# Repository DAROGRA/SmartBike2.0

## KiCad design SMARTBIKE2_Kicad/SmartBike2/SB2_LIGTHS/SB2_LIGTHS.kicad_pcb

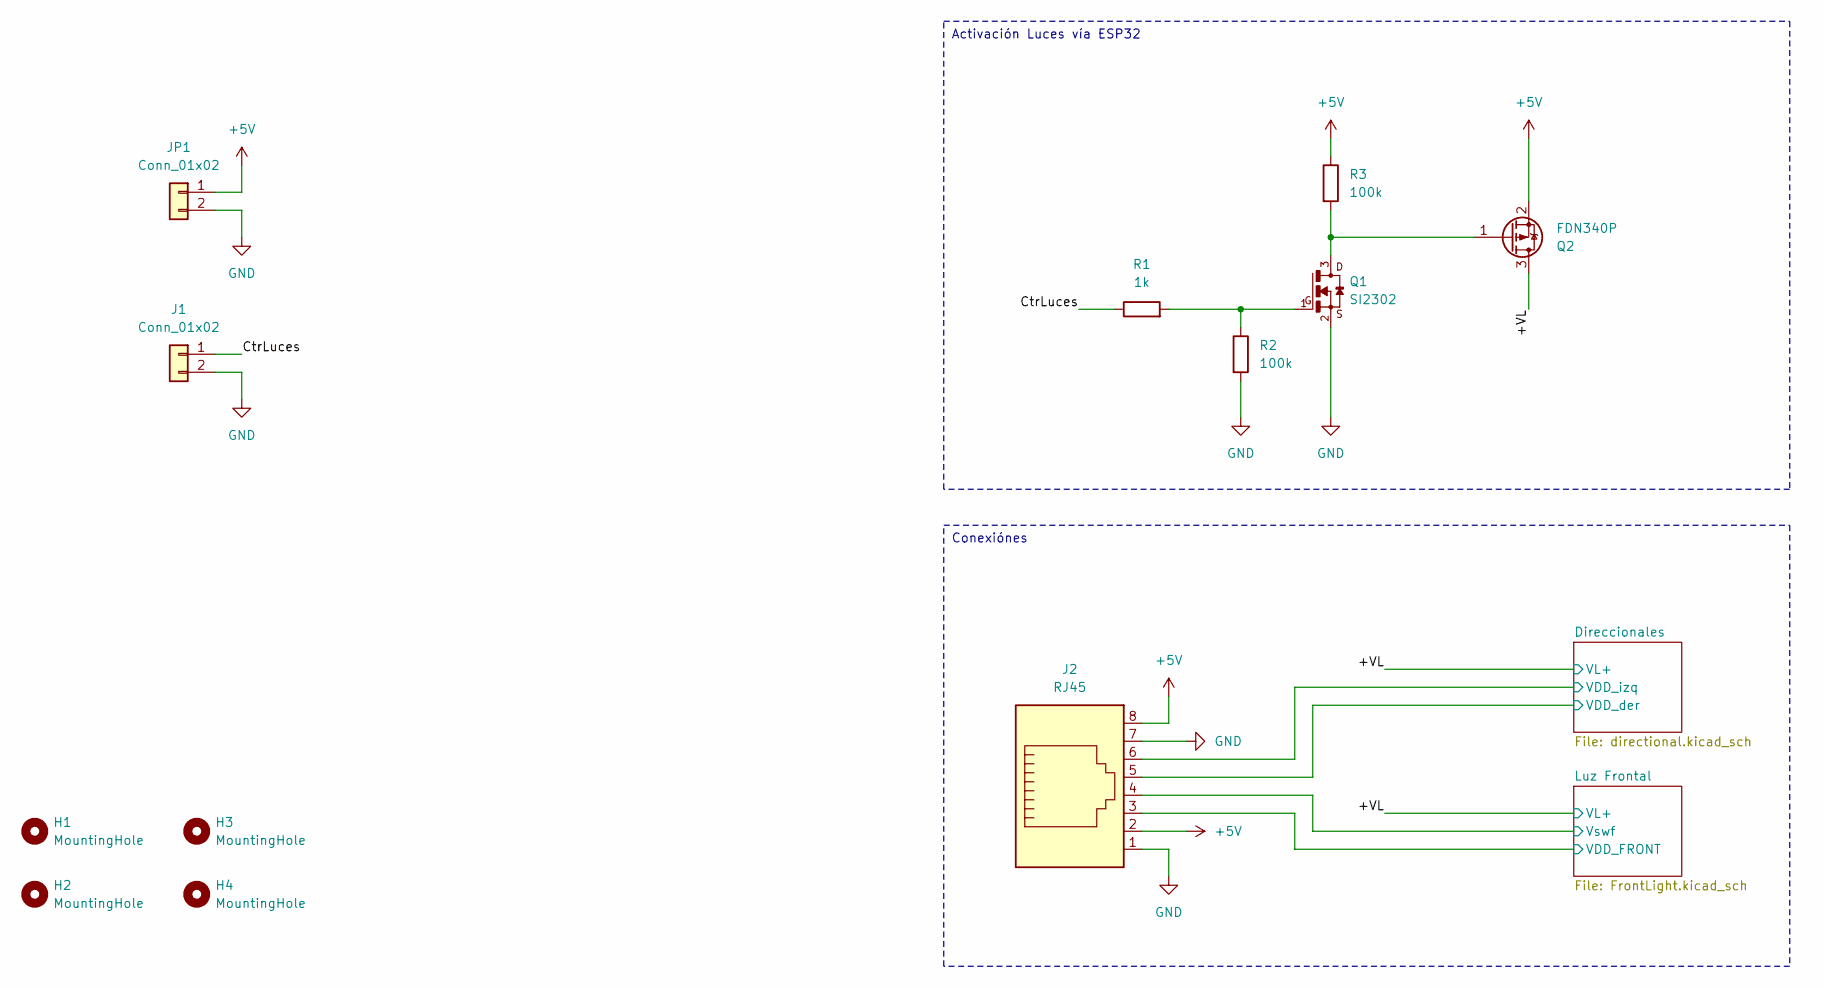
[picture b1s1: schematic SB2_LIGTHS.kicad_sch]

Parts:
H1, H2, H3, H4: MountingHole; MountingHole_2.2mm_M2
J1: Conn_01x02; JST_XH_B2B-XH-A_1x02_P2.50mm_Vertical
J2: RJ45; RJ45_Amphenol_RJHSE538X
JP1: Conn_01x02; JST_XH_B2B-XH-A_1x02_P2.50mm_Vertical
Q1: SI2302; SOT-23
Q2: FDN340P; SuperSOT-3
R1: 1k; R_0805_2012Metric_Pad1.20x1.40mm_HandSolder
R2, R3: 100k; R_0805_2012Metric_Pad1.20x1.40mm_HandSolder

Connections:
+5V: J2.2, J2.8, JP1.1, Q2.2 (S), R3.1
/+VL: Q2.3 (D); also elsewhere on the board
/CtrLuces: J1.1, R1.1
/Direccionales/VDD_der: J2.5; also elsewhere on the board
/Direccionales/VDD_izq: J2.6; also elsewhere on the board
/Luz Frontal/VDD_FRONT: J2.3; also elsewhere on the board
/Luz Frontal/Vswf: J2.4; also elsewhere on the board
GND: J1.2, J2.1, J2.7, JP1.2, Q1.2, R2.2; also elsewhere on the board
unnamed: Q1.1, R1.2, R2.1
unnamed: Q1.3, Q2.1 (G), R3.2

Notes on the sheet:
Activación Luces vía ESP32
Conexiónes

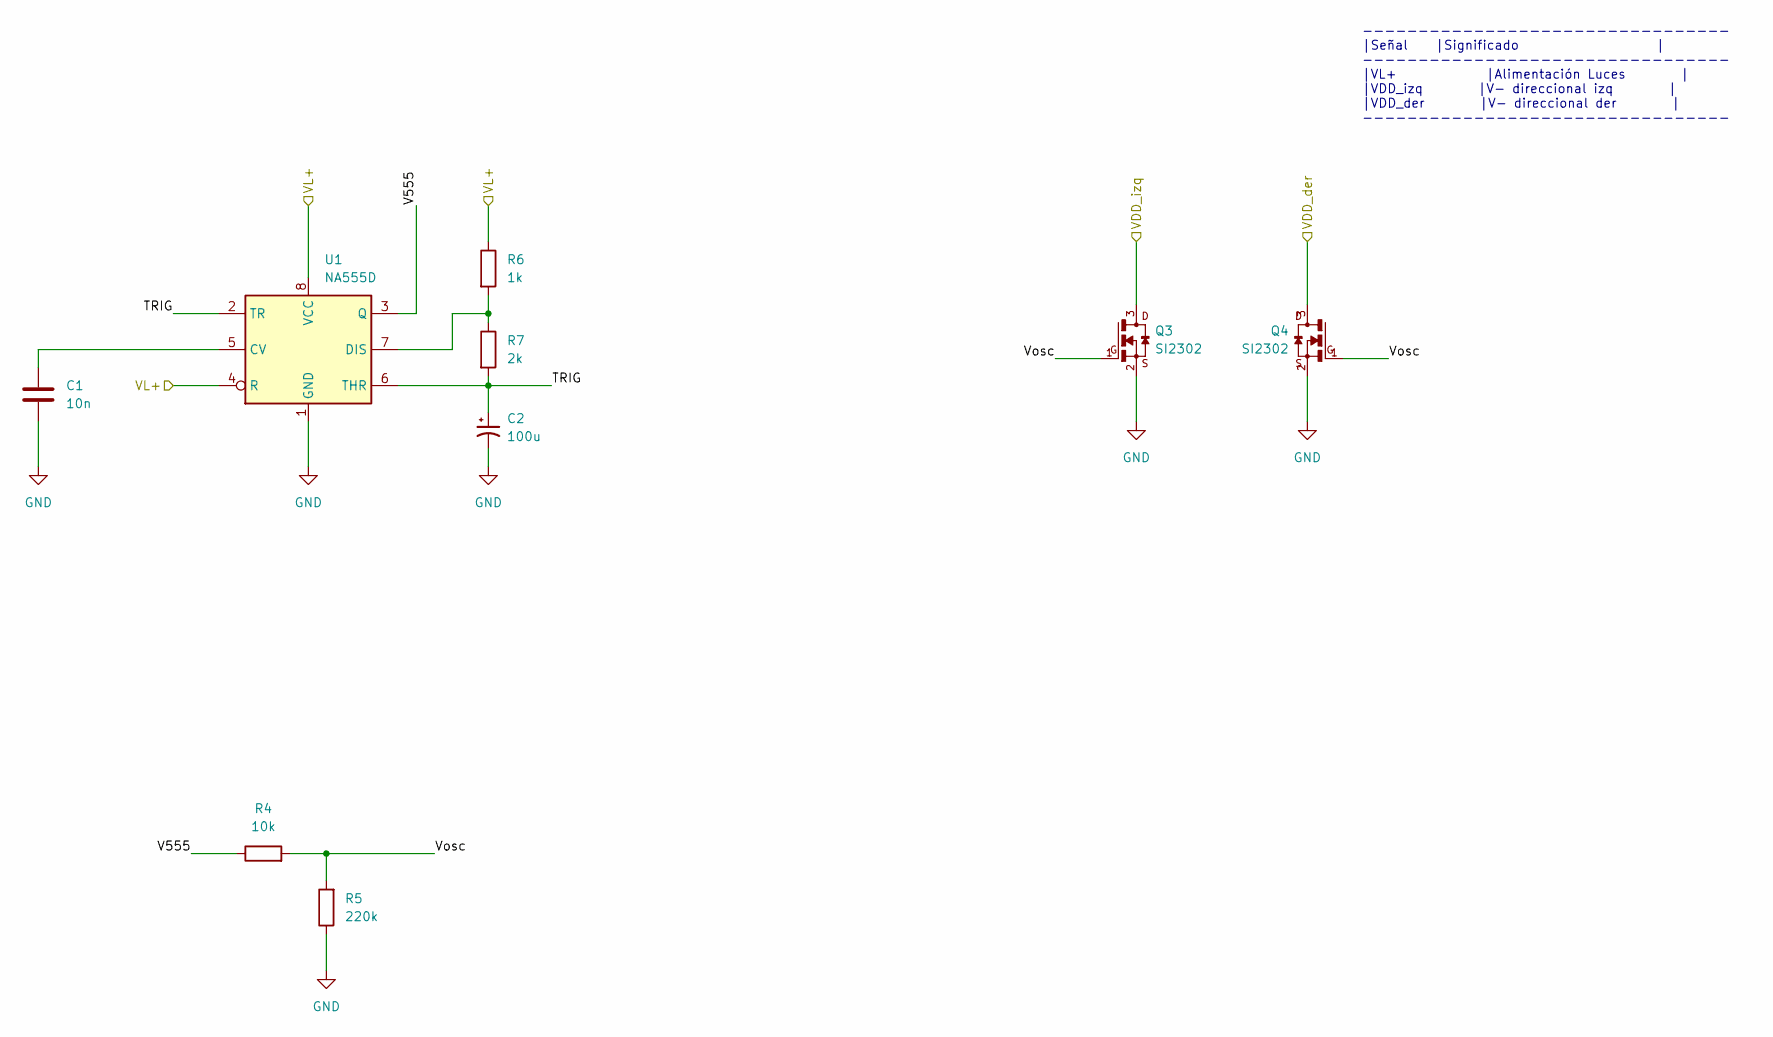
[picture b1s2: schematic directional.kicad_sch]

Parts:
C1: 10n; C_0805_2012Metric_Pad1.18x1.45mm_HandSolder
C2: 100u; CP_Elec_6.3x5.4
Q3, Q4: SI2302; SOT-23
R4: 10k; R_0805_2012Metric_Pad1.20x1.40mm_HandSolder
R5: 220k; R_0805_2012Metric_Pad1.20x1.40mm_HandSolder
R6: 1k; R_0805_2012Metric_Pad1.20x1.40mm_HandSolder
R7: 2k; R_0805_2012Metric_Pad1.20x1.40mm_HandSolder
U1: NA555D; SOIC-8_3.9x4.9mm_P1.27mm

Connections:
/+VL: R6.1, U1.4 (R), U1.8 (VCC); also elsewhere on the board
/Direccionales/TRIG: C2.1, R7.2, U1.2 (TR), U1.6 (THR)
/Direccionales/V555: R4.1, U1.3 (Q)
/Direccionales/VDD_der: Q4.3; also elsewhere on the board
/Direccionales/VDD_izq: Q3.3; also elsewhere on the board
/Direccionales/Vosc: Q3.1, Q4.1, R4.2, R5.2
GND: C1.2, C2.2, Q3.2, Q4.2, R5.1, U1.1 (GND); also elsewhere on the board
unnamed: C1.1, U1.5 (CV)
unnamed: R6.2, R7.1, U1.7 (DIS)

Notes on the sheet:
--------------------------------- |Señal |Significado | --------------------------------- |VL+ |Alimentación Luces | |VDD_izq |V- direccional izq | |VDD_der |V- direccional der | ---------------------------------

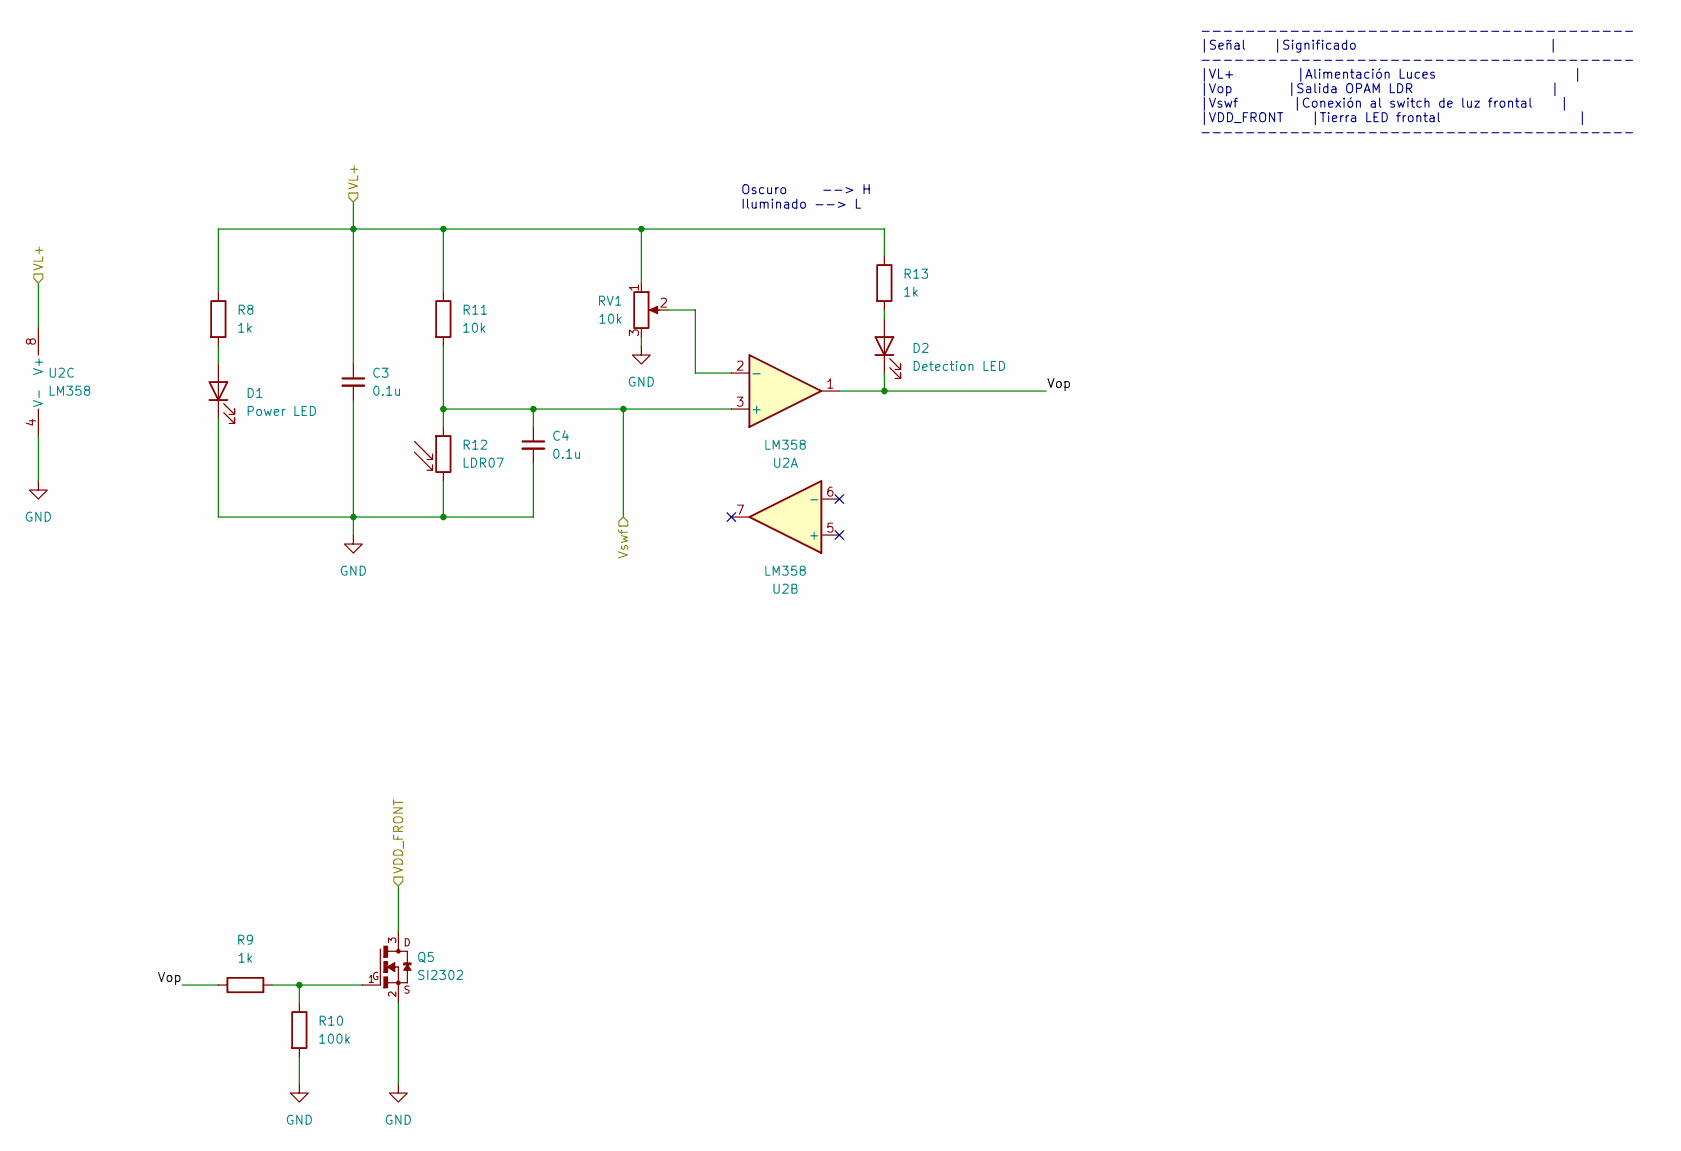
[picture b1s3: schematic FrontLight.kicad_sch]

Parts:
C3, C4: 0.1u; C_0805_2012Metric_Pad1.18x1.45mm_HandSolder
D1: Power LED; LED_1206_3216Metric_Pad1.42x1.75mm_HandSolder
D2: Detection LED; LED_1206_3216Metric_Pad1.42x1.75mm_HandSolder
Q5: SI2302; SOT-23
R8, R9, R13: 1k; R_0805_2012Metric_Pad1.20x1.40mm_HandSolder
R10: 100k; R_0805_2012Metric_Pad1.20x1.40mm_HandSolder
R11: 10k; R_0805_2012Metric_Pad1.20x1.40mm_HandSolder
R12: LDR07; R_LDR_5.1x4.3mm_P3.4mm_Vertical
RV1: 10k; Potentiometer_Bourns_3386P_Vertical
U2: LM358; SO-8_3.9x4.9mm_P1.27mm

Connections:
/+VL: C3.1, R8.1, R11.1, R13.1, RV1.1, U2.8 (V+); also elsewhere on the board
/Luz Frontal/VDD_FRONT: Q5.3; also elsewhere on the board
/Luz Frontal/Vop: D2.1 (K), R9.1, U2.1
/Luz Frontal/Vswf: C4.1, R11.2, R12.1, U2.3 (+); also elsewhere on the board
GND: C3.2, C4.2, D1.1 (K), Q5.2, R10.2, R12.2, RV1.3, U2.4 (V-); also elsewhere on the board
unnamed: D1.2 (A), R8.2
unnamed: D2.2 (A), R13.2
unnamed: Q5.1, R9.2, R10.1
unnamed: RV1.2, U2.2 (-)

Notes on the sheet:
Oscuro --> H Iluminado --> L
--------------------------------------- |Señal |Significado | --------------------------------------- |VL+ |Alimentación Luces | |Vop |Salida OPAM LDR | |Vswf |Conexión al switch de luz frontal | |VDD_FRONT |Tierra LED frontal | ---------------------------------------

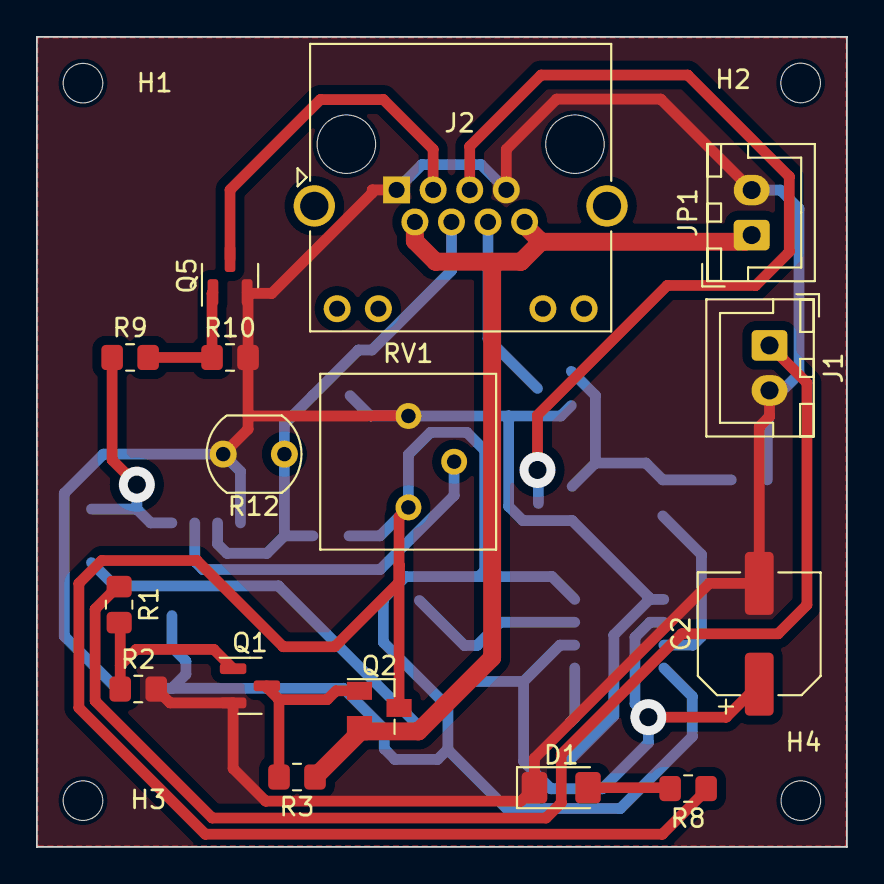
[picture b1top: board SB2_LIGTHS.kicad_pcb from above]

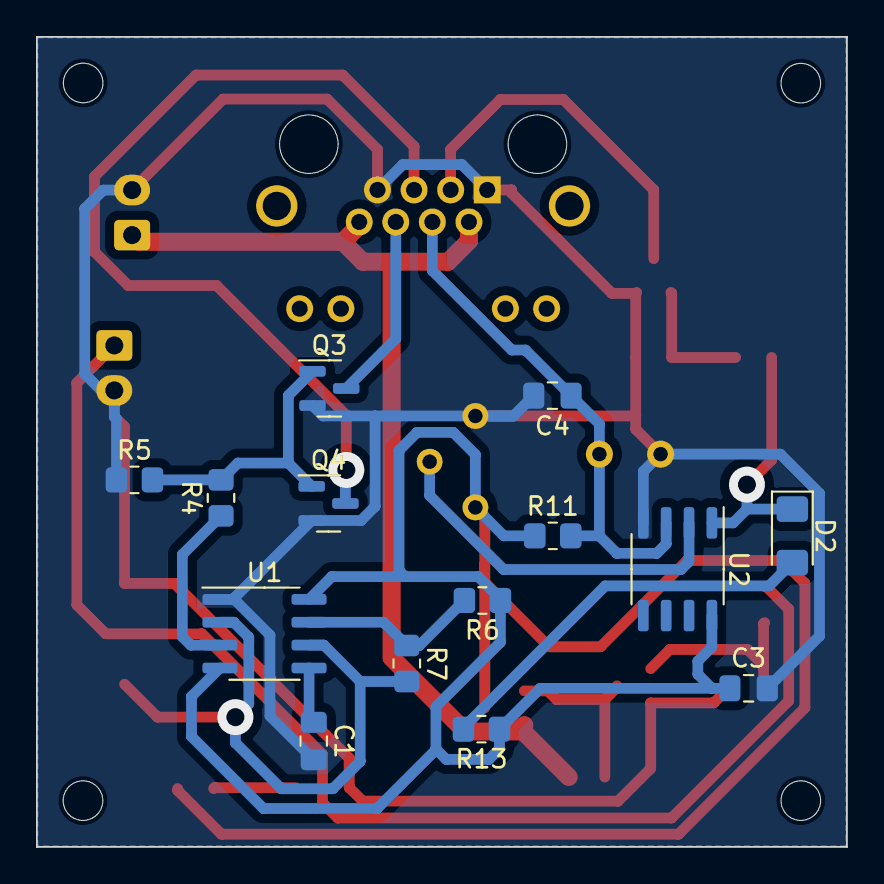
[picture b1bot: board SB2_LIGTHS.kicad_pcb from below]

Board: 2 copper layers, 45.0 x 45.0 mm, 34 parts (14 on the bottom side), 20 nets.

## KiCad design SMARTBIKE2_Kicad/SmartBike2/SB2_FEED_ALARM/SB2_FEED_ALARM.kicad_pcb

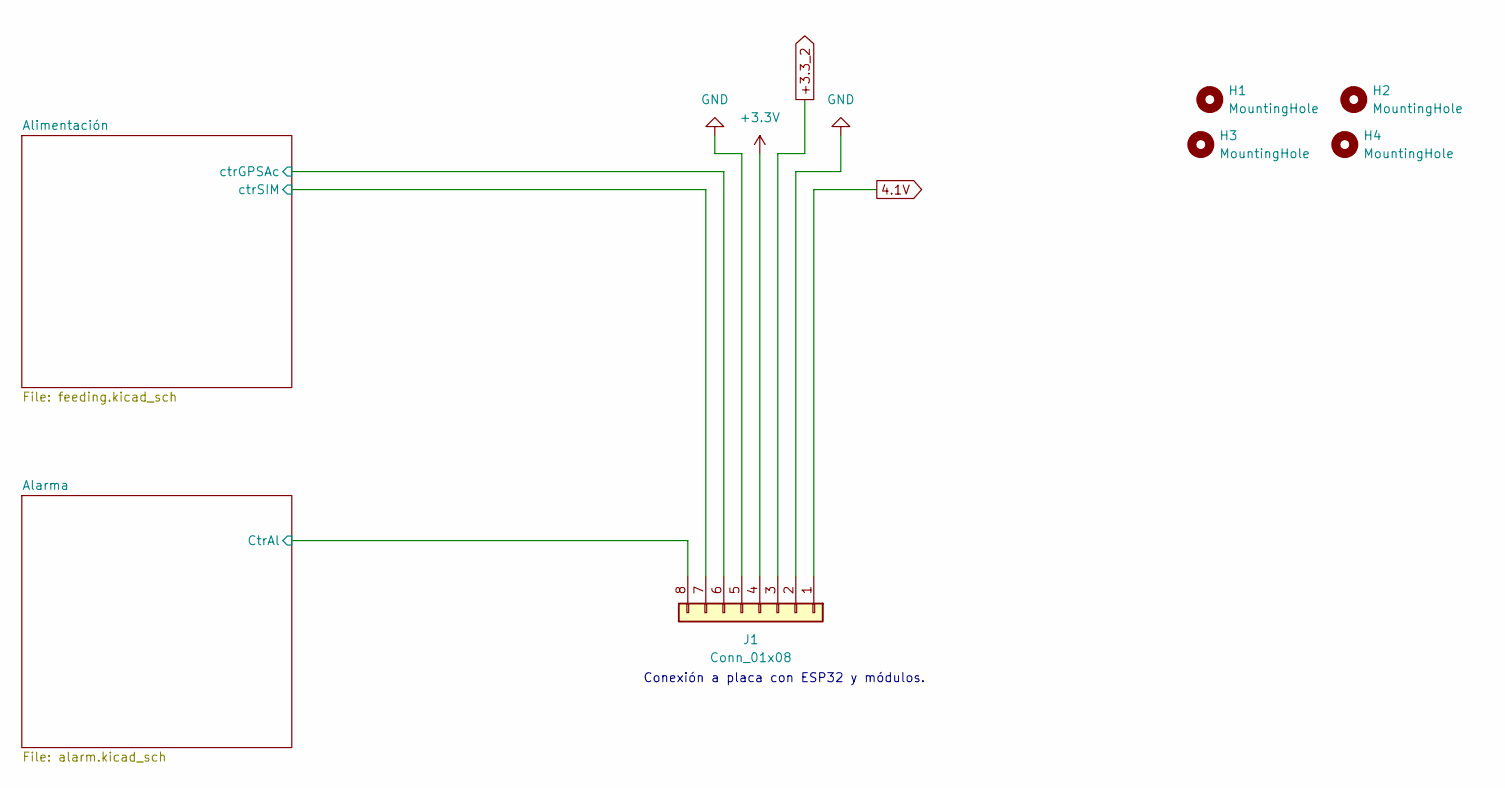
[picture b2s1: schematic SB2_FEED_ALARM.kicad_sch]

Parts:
H1, H2, H3, H4: MountingHole; MountingHole_2.2mm_M2
J1: Conn_01x08; JST_XH_B8B-XH-A_1x08_P2.50mm_Vertical

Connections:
4.1V: J1.1; also elsewhere on the board
+3.3V: J1.4; also elsewhere on the board
+3.3_2: J1.3; also elsewhere on the board
/Alarma/CtrAl: J1.8; also elsewhere on the board
/Alimentación/ctrGPSAc: J1.6; also elsewhere on the board
/Alimentación/ctrSIM: J1.7; also elsewhere on the board
GND: J1.2, J1.5; also elsewhere on the board

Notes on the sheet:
Conexión a placa con ESP32 y módulos.

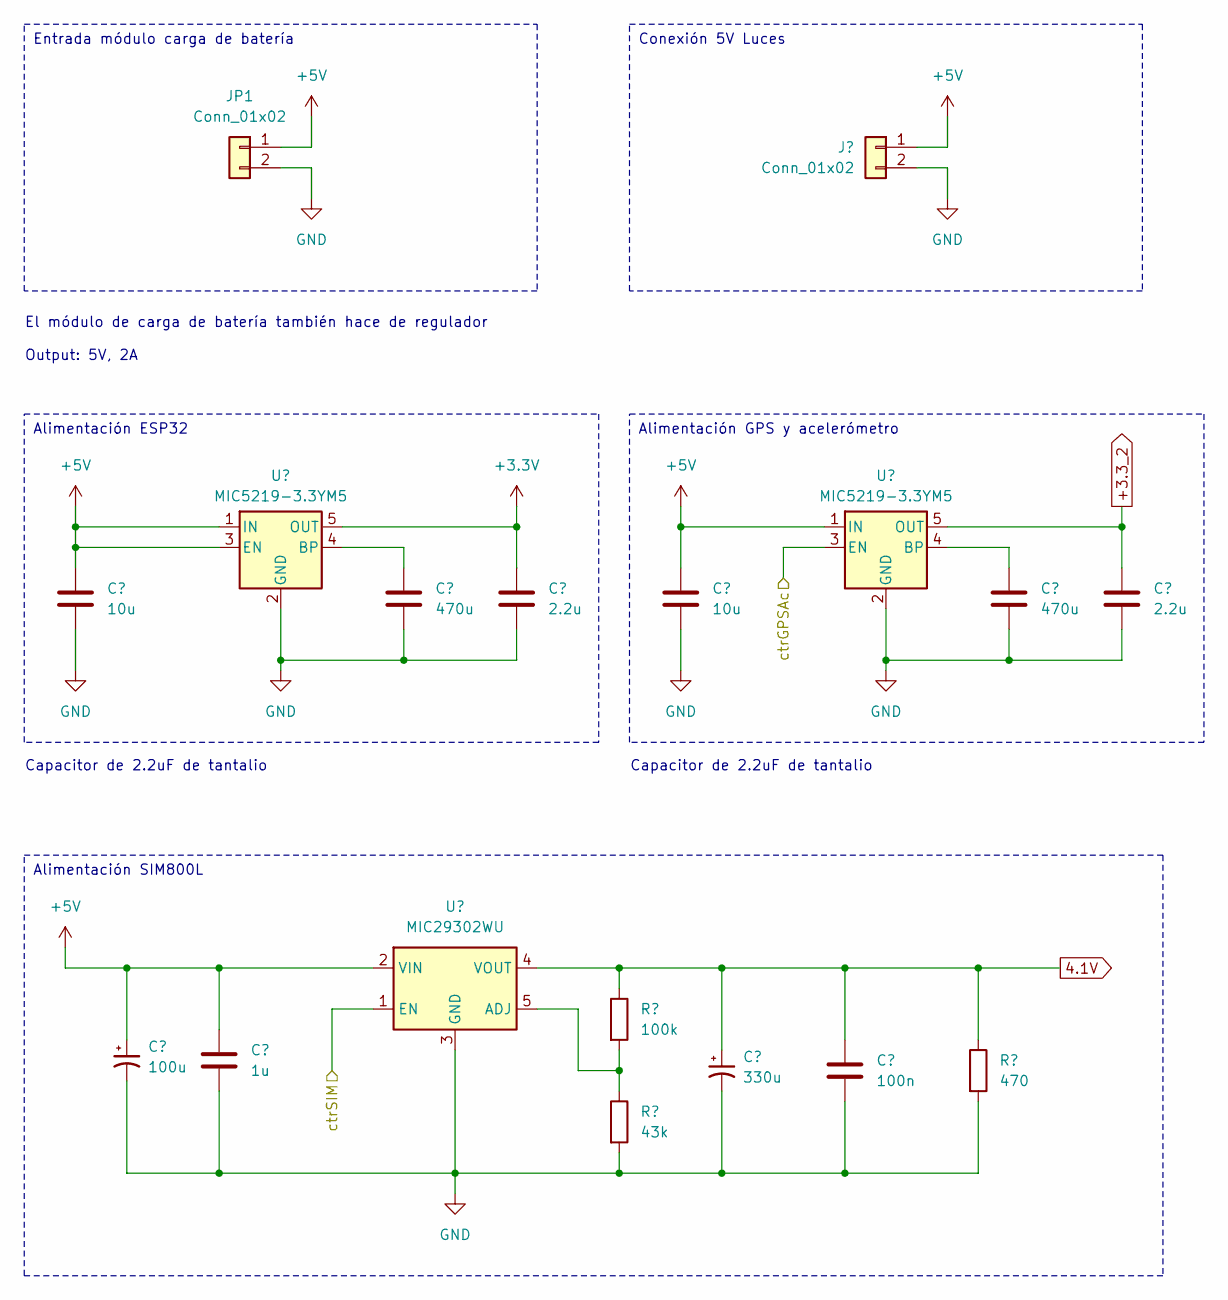
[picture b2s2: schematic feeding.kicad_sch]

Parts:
C1, C6: 10u; C_1206_3216Metric_Pad1.33x1.80mm_HandSolder
C2: 100u; CP_Elec_6.3x5.4
C3: 1u; C_0805_2012Metric_Pad1.18x1.45mm_HandSolder
C4, C9: 470u; C_Elec_8x10.2
C5: 2.2u; CP_EIA-3216-10_Kemet-I_Pad1.58x1.35mm_HandSolder
C7: 330u; CP_Elec_8x10
C8: 100n; C_0805_2012Metric_Pad1.18x1.45mm_HandSolder
C10: 2.2u; CP_EIA-3216-18_Kemet-A_Pad1.58x1.35mm_HandSolder
J2: Conn_01x02; JST_EH_B2B-EH-A_1x02_P2.50mm_Vertical
JP1: Conn_01x02; JST_EH_B2B-EH-A_1x02_P2.50mm_Vertical
R1: 100k; R_0805_2012Metric_Pad1.20x1.40mm_HandSolder
R2: 43k; R_0805_2012Metric_Pad1.20x1.40mm_HandSolder
R3: 470; R_0805_2012Metric_Pad1.20x1.40mm_HandSolder
U1, U3: MIC5219-3.3YM5; SOT-23-5
U2: MIC29302WU; TO-263-5_TabPin3

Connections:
4.1V: C7.1, C8.1, R1.1, R3.1, U2.4 (VOUT); also elsewhere on the board
+3.3V: C5.1, U1.5 (OUT); also elsewhere on the board
+3.3_2: C10.1, U3.5 (OUT); also elsewhere on the board
+5V: C1.1, C2.1, C3.1, C6.1, J2.1, JP1.1, U1.1 (IN), U1.3 (EN), U2.2 (VIN), U3.1 (IN); also elsewhere on the board
/Alimentación/ctrGPSAc: U3.3 (EN); also elsewhere on the board
/Alimentación/ctrSIM: U2.1 (EN); also elsewhere on the board
GND: C1.2, C2.2, C3.2, C4.2, C5.2, C6.2, C7.2, C8.2, C9.2, C10.2, J2.2, JP1.2, R2.2, R3.2, U1.2 (GND), U2.3 (GND), U3.2 (GND); also elsewhere on the board
unnamed: C4.1, U1.4 (BP)
unnamed: R1.2, R2.1, U2.5 (ADJ)
unnamed: C9.1, U3.4 (BP)

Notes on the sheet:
Entrada módulo carga de batería
Conexión 5V Luces
Alimentación SIM800L
Alimentación ESP32
Alimentación GPS y acelerómetro
El módulo de carga de batería también hace de regulador Output: 5V, 2A
Capacitor de 2.2uF de tantalio

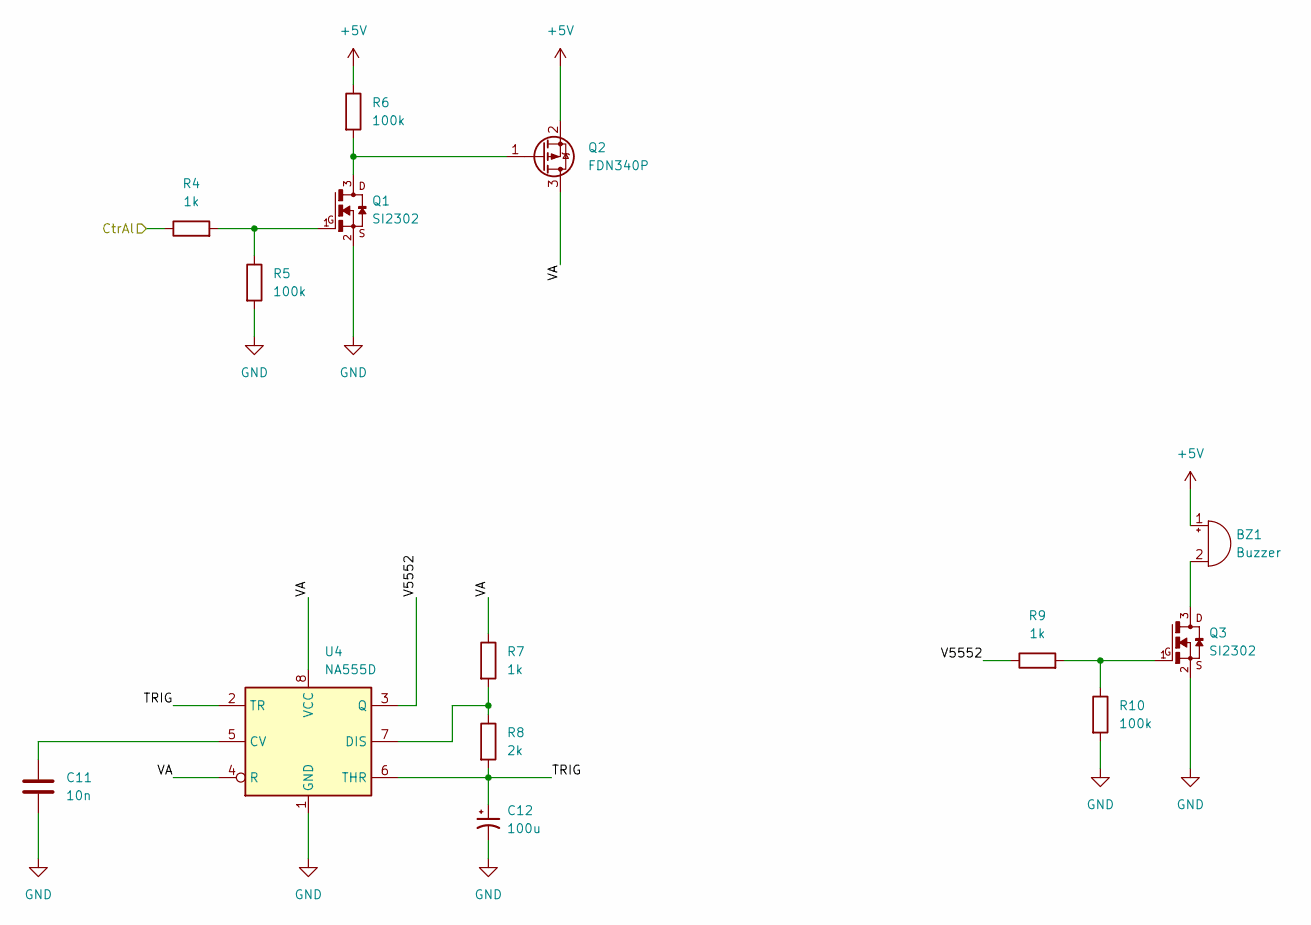
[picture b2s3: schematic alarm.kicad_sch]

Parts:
BZ1: Buzzer; PinHeader_1x02_P2.54mm_Vertical
C11: 10n; C_0805_2012Metric_Pad1.18x1.45mm_HandSolder
C12: 100u; CP_Elec_6.3x5.4
Q1, Q3: SI2302; SOT-23
Q2: FDN340P; SuperSOT-3
R4, R7, R9: 1k; R_0805_2012Metric_Pad1.20x1.40mm_HandSolder
R5, R6, R10: 100k; R_0805_2012Metric_Pad1.20x1.40mm_HandSolder
R8: 2k; R_0805_2012Metric_Pad1.20x1.40mm_HandSolder
U4: NA555D; SOIC-8_3.9x4.9mm_P1.27mm

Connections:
+5V: BZ1.1 (-), Q2.2 (S), R6.1; also elsewhere on the board
/Alarma/CtrAl: R4.1; also elsewhere on the board
/Alarma/TRIG: C12.1, R8.2, U4.2 (TR), U4.6 (THR)
/Alarma/V5552: R9.1, U4.3 (Q)
/Alarma/VA: Q2.3 (D), R7.1, U4.4 (R), U4.8 (VCC)
GND: C11.2, C12.2, Q1.2, Q3.2, R5.2, R10.2, U4.1 (GND); also elsewhere on the board
unnamed: BZ1.2 (+), Q3.3
unnamed: Q1.1, R4.2, R5.1
unnamed: Q1.3, Q2.1 (G), R6.2
unnamed: Q3.1, R9.2, R10.1
unnamed: C11.1, U4.5 (CV)
unnamed: R7.2, R8.1, U4.7 (DIS)

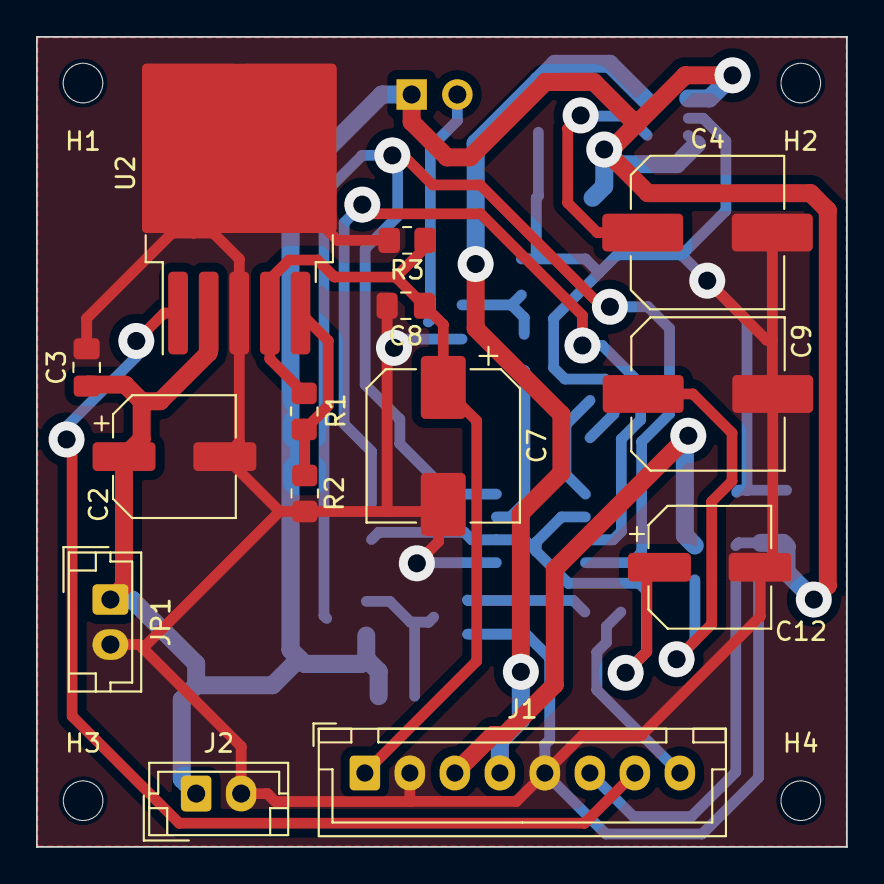
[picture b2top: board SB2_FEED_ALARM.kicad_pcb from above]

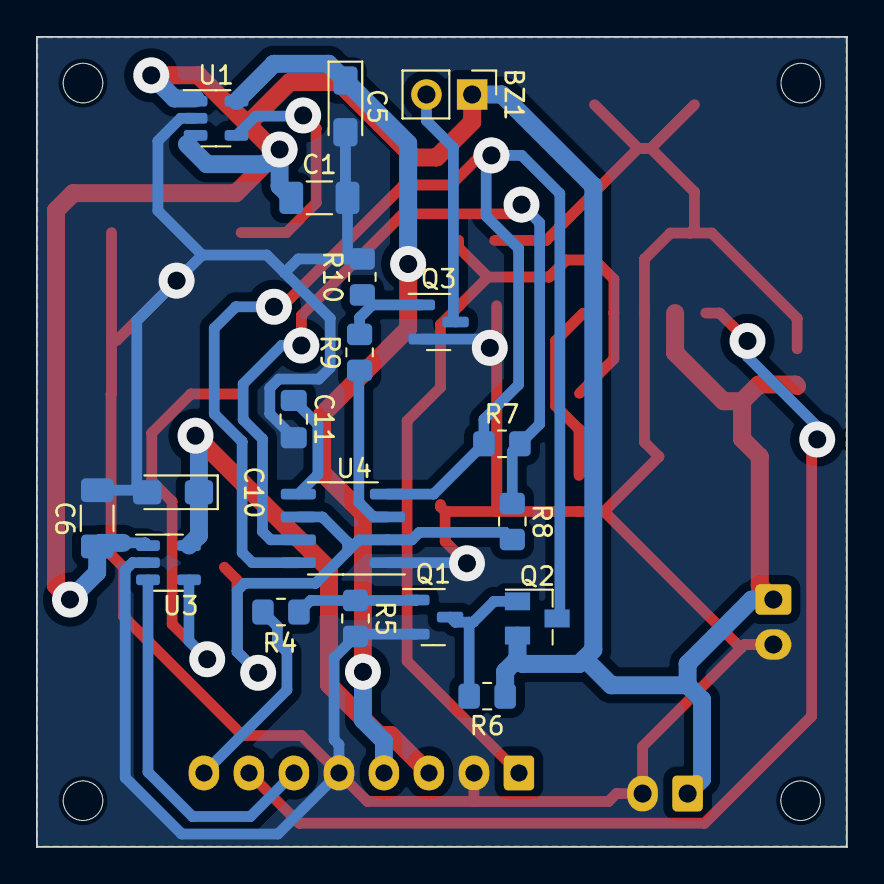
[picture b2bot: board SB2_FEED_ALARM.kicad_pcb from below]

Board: 2 copper layers, 45.0 x 45.0 mm, 37 parts (19 on the bottom side), 20 nets.

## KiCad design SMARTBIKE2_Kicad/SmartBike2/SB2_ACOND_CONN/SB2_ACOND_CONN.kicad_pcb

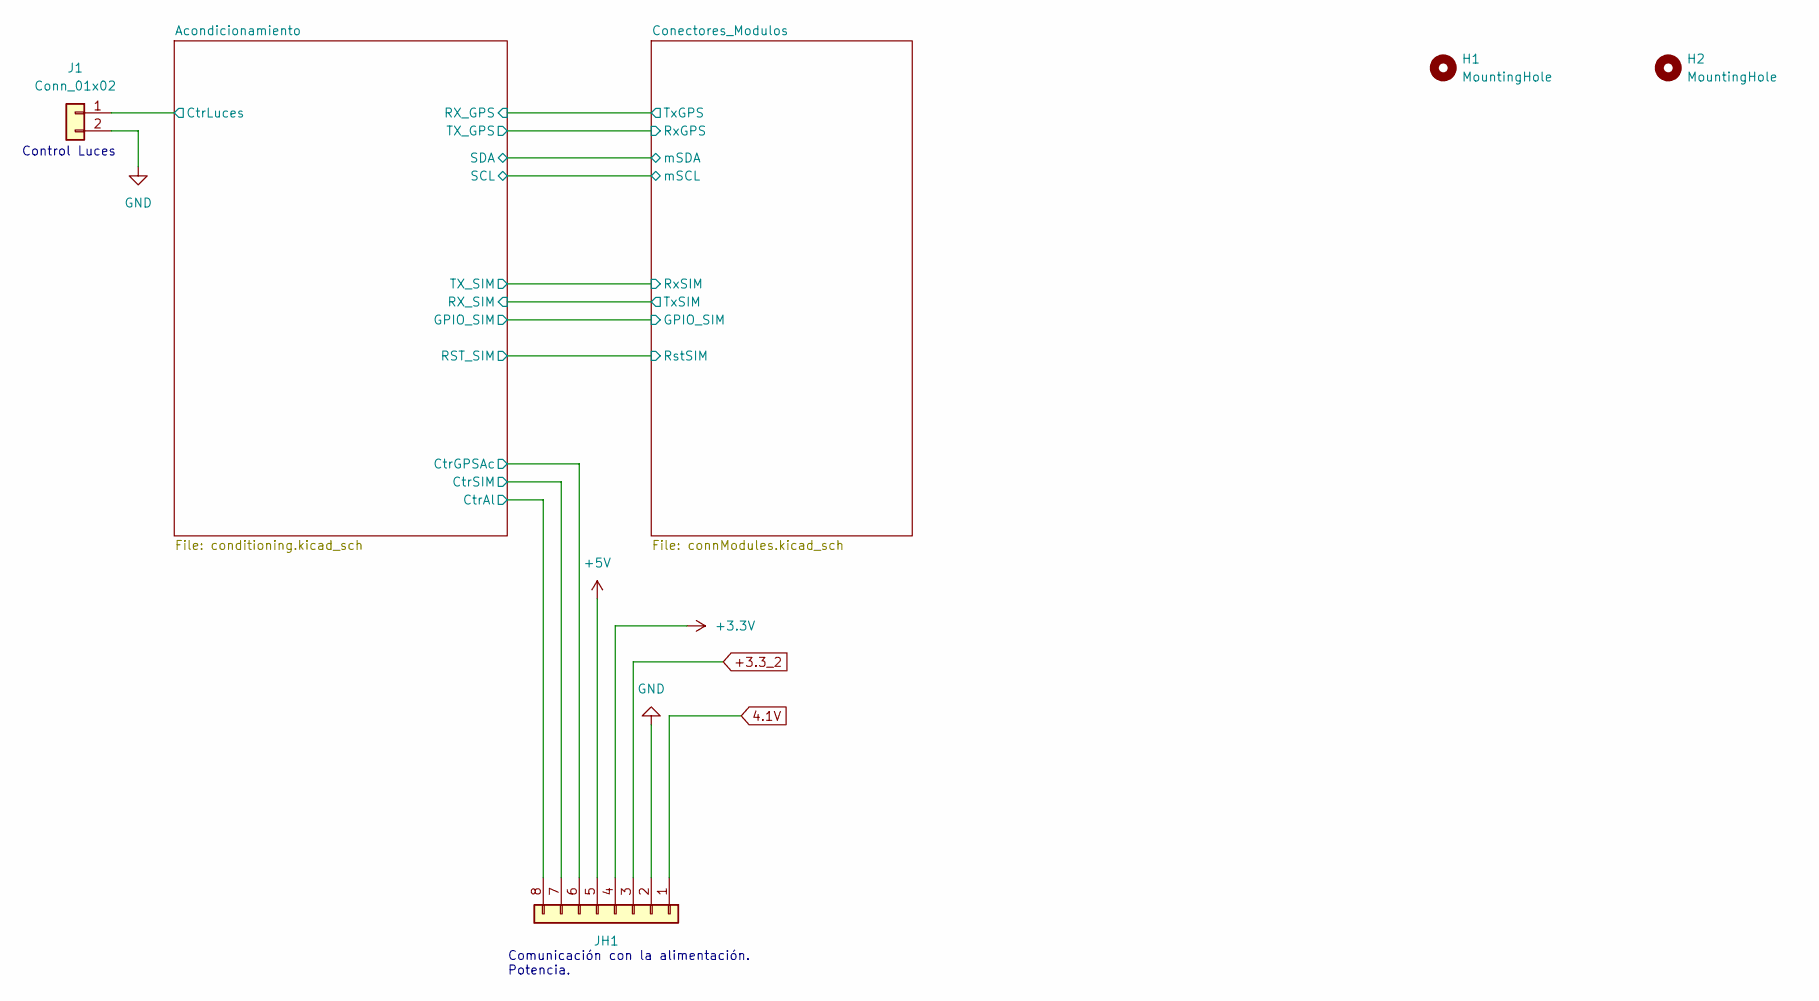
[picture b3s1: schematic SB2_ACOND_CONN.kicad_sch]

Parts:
H1, H2: MountingHole; MountingHole_2.2mm_M2
J1: Conn_01x02; JST_EH_B2B-EH-A_1x02_P2.50mm_Vertical
JH1: JST_XH_B8B-XH-A_1x08_P2.50mm_Vertical

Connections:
4.1V: JH1.1; also elsewhere on the board
+3.3V: JH1.4; also elsewhere on the board
+3.3_2: JH1.3; also elsewhere on the board
+5V: JH1.5; also elsewhere on the board
/Acondicionamiento/CtrAl: JH1.8; also elsewhere on the board
/Acondicionamiento/CtrGPSAc: JH1.6; also elsewhere on the board
/Acondicionamiento/CtrLuces: J1.1; also elsewhere on the board
/Acondicionamiento/CtrSIM: JH1.7; also elsewhere on the board
GND: J1.2, JH1.2; also elsewhere on the board

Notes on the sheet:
Control Luces
Comunicación con la alimentación. Potencia.

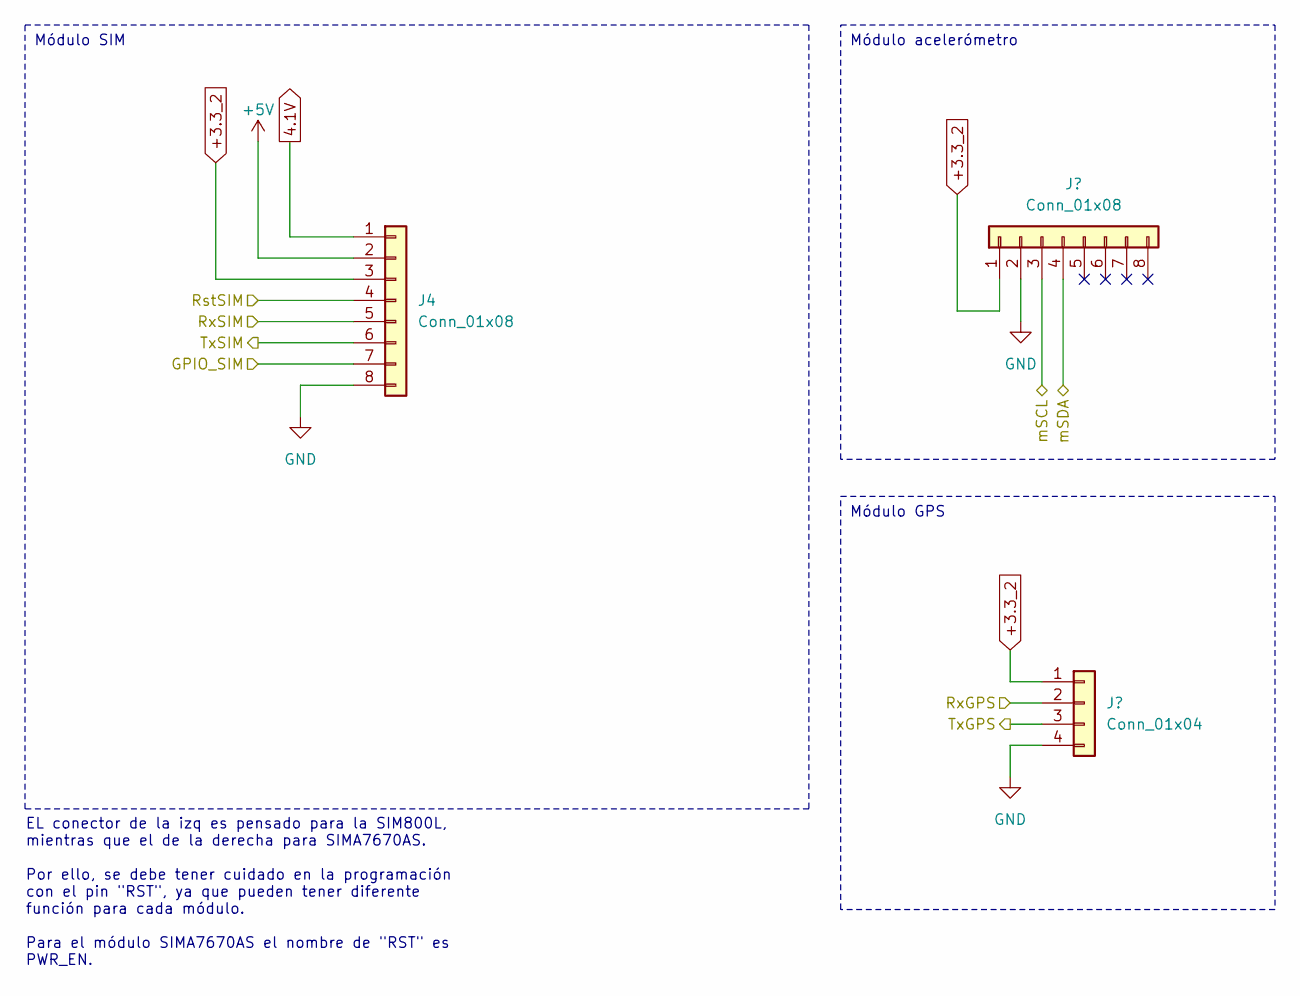
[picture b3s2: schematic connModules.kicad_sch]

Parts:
J4: Conn_01x08; PinHeader_1x08_P2.54mm_Vertical
J5: Conn_01x08; PinSocket_1x08_P2.54mm_Vertical
J6: Conn_01x04; PinSocket_1x04_P2.54mm_Vertical

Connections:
4.1V: J4.1; also elsewhere on the board
+3.3_2: J4.3, J5.1, J6.1; also elsewhere on the board
+5V: J4.2; also elsewhere on the board
/Acondicionamiento/GPIO_SIM: J4.7; also elsewhere on the board
/Acondicionamiento/RST_SIM: J4.4; also elsewhere on the board
/Acondicionamiento/RX_GPS: J6.3; also elsewhere on the board
/Acondicionamiento/RX_SIM: J4.6; also elsewhere on the board
/Acondicionamiento/SCL: J5.3; also elsewhere on the board
/Acondicionamiento/SDA: J5.4; also elsewhere on the board
/Acondicionamiento/TX_GPS: J6.2; also elsewhere on the board
/Acondicionamiento/TX_SIM: J4.5; also elsewhere on the board
GND: J4.8, J5.2, J6.4; also elsewhere on the board

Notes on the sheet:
Módulo SIM
Módulo acelerómetro
Módulo GPS
EL conector de la izq es pensado para la SIM800L, mientras que el de la derecha para SIMA7670AS. Por ello, se debe tener cuidado en la programación con el pin "RST", ya que pueden tener diferente función para cada módulo. Para el módulo SIMA7670AS el nombre de "RST" es PWR_EN.
